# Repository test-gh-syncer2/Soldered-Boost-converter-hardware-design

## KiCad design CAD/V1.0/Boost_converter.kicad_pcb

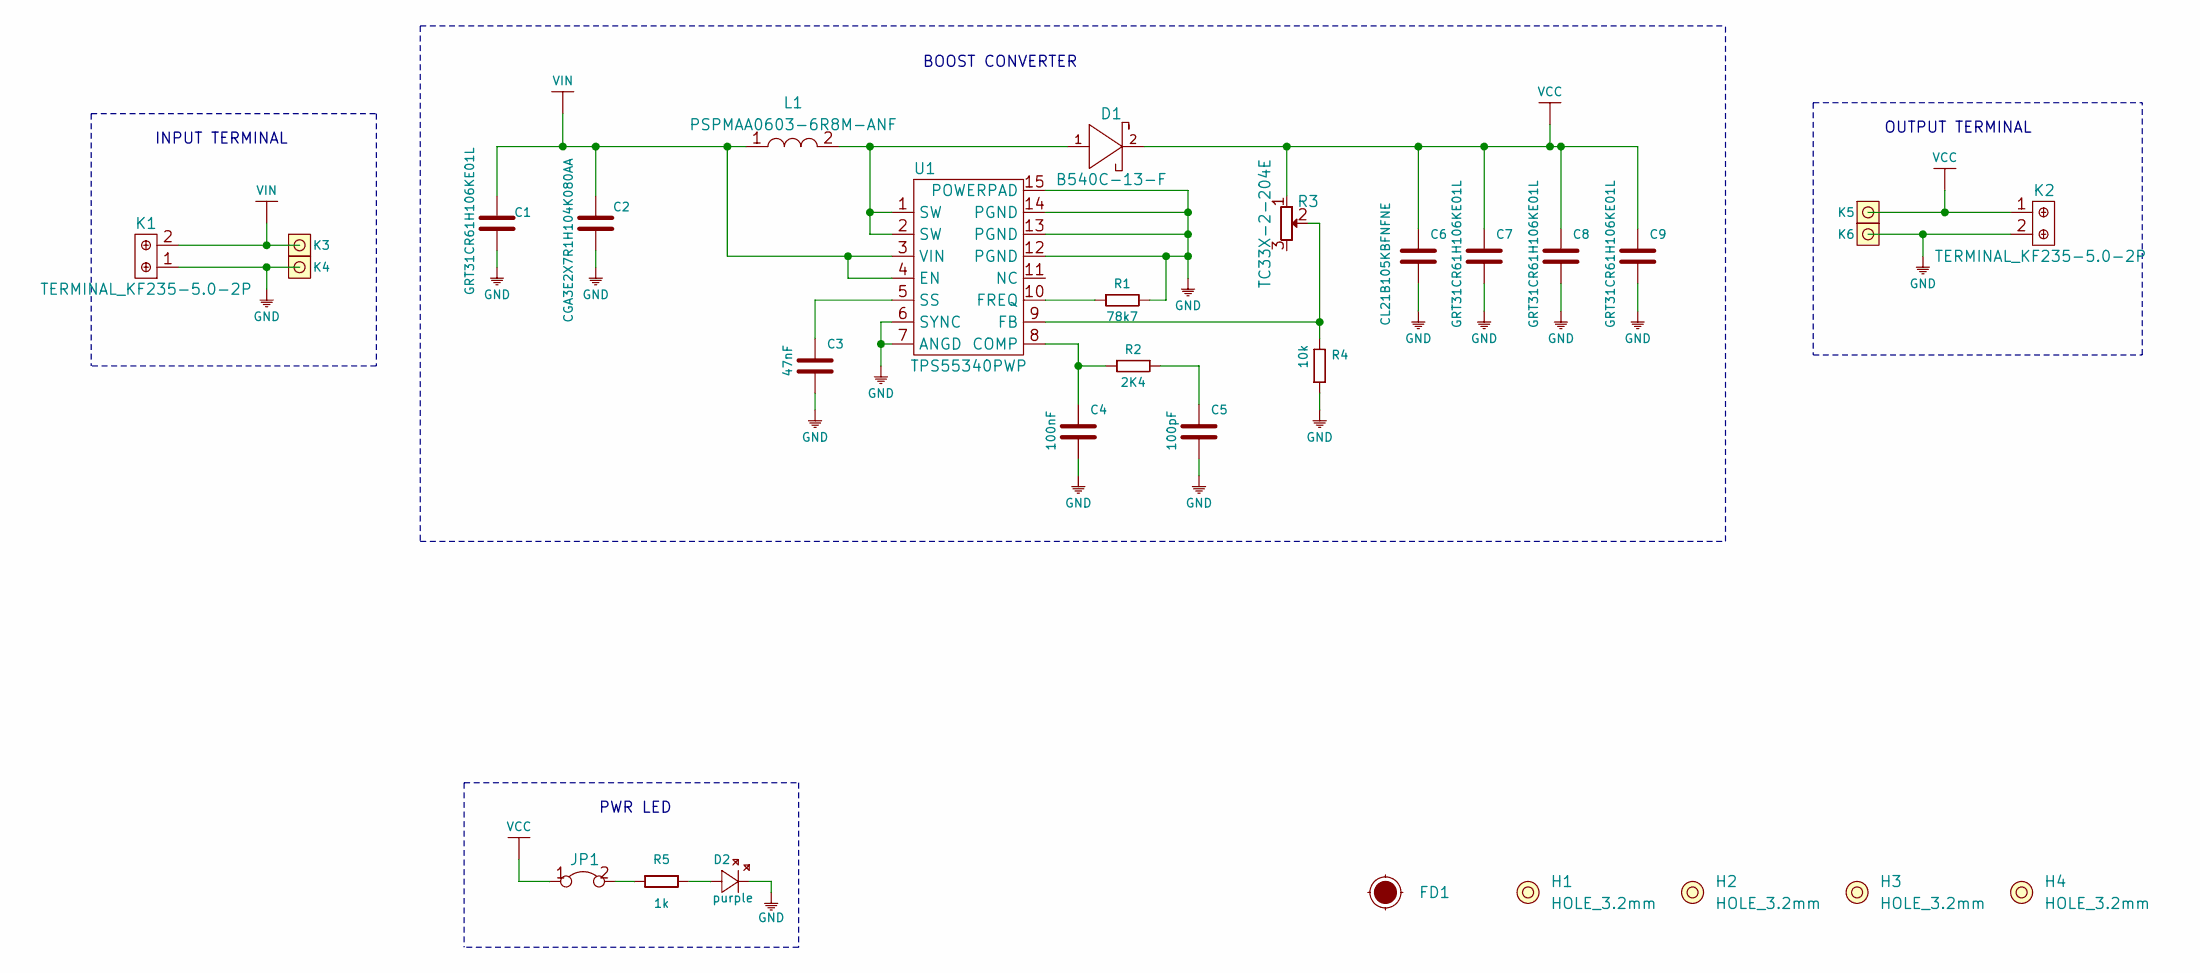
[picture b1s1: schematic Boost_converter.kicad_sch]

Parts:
C1, C7, C8, C9: GRT31CR61H106KE01L; 1206C
C2: CGA3E2X7R1H104K080AA; 0603C
C3: 47nF; 0603C
C4: 100nF; 0603C
C5: 100pF; 0603C
C6: CL21B105KBFNFNE; 0805C
D1: B540C-13-F; M4_DIODA
D2: purple; 0402LED
FD1: Fiducial_Stencil; FIDUCIAL_1MM_PASTE
H1, H2, H3, H4: HOLE_3.2mm
JP1: SMD-JUMPER-CONNECTED_TRACE_NOSLODERMASK
K1, K2: TERMINAL_KF235-5.0-2P
K3, K4, K5, K6: HEADER_MALE_1X1
L1: PSPMAA0603-6R8M-ANF; Inductor_SMD_7x6.6
R1: 78k7; 0603R
R2: 2K4; 0603R
R3: TC33X-2-204E; tc33x-2-103e
R4: 10k; 0603R
R5: 1k; 0402R
U1: TPS55340PWP; TPS55340

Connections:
GND: C1.1, C2.1, C3.1, C4.1, C5.1, C6.1, C7.1, C8.1, C9.1, D2.2 (K), K1.1, K2.2, K4.1, K6.1, R1.2, R4.1, U1.6 (SYNC), U1.7 (ANGD), U1.12 (PGND), U1.13 (PGND), U1.14 (PGND), U1.15 (POWERPAD)
unnamed: C3.2, U1.5 (SS)
unnamed: C4.2, R2.1, U1.8 (COMP)
unnamed: C5.2, R2.2
unnamed: D1.1 (A), L1.2, U1.1 (SW), U1.2 (SW)
unnamed: D2.1 (A), R5.2
unnamed: JP1.2, R5.1
unnamed: R1.1, U1.10 (FREQ)
unnamed: R3.2, R4.2, U1.9 (FB)
VCC: C6.2, C7.2, C8.2, C9.2, D1.2 (K), JP1.1, K2.1, K5.1, R3.1
VIN: C1.2, C2.2, K1.2, K3.1, L1.1, U1.3 (VIN), U1.4 (EN)

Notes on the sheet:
INPUT TERMINAL
PWR LED
BOOST CONVERTER
OUTPUT TERMINAL

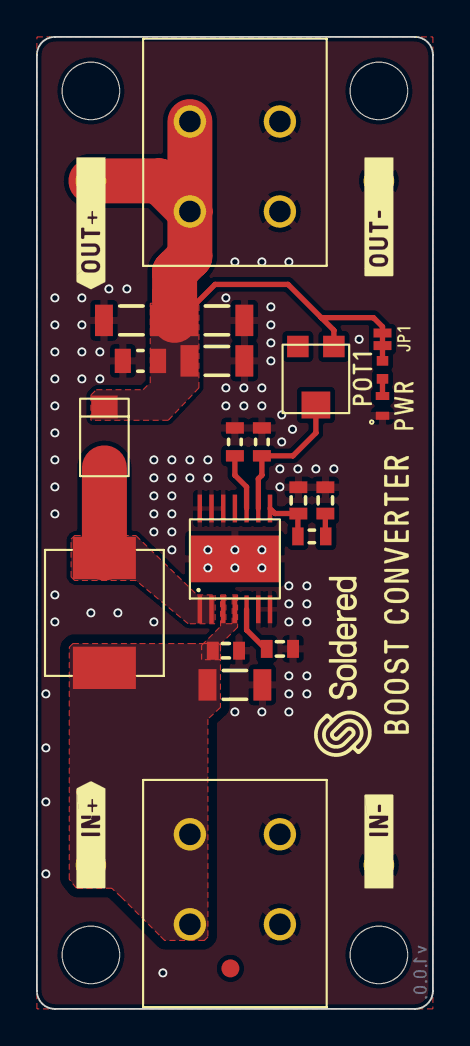
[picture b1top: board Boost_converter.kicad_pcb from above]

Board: 2 copper layers, 22.0 x 54.0 mm, 30 parts (0 on the bottom side), 11 nets.

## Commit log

2021-09-23 Syncing to git
2021-09-23 Updating open source files.
